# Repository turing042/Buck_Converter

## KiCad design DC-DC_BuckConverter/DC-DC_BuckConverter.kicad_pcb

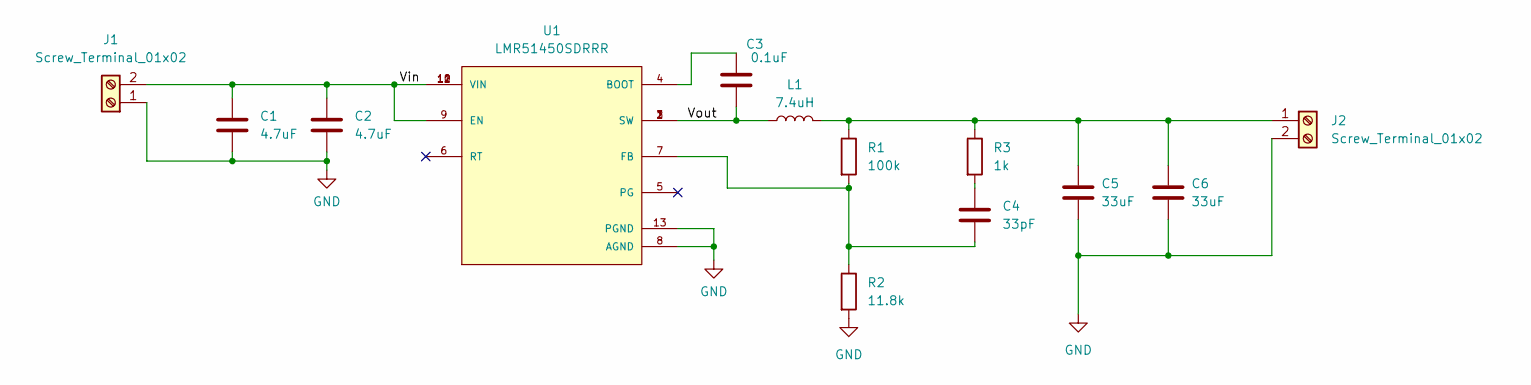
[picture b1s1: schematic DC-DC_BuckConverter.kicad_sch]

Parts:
C1, C2: 4.7uF; C_0603_1608Metric
C3: 0.1uF; C_0603_1608Metric
C4: 33pF; C_0603_1608Metric
C5, C6: 33uF; C_0603_1608Metric
J1, J2: Screw_Terminal_01x02; PhoenixContact_MSTBA_2,5_2-G-5,08_1x02_P5.08mm_Horizontal
L1: 7.4uH; L_Vishay_IHSM-4825
R1: 100k; R_0603_1608Metric
R2: 11.8k; R_0603_1608Metric
R3: 1k; R_0603_1608Metric
U1: LMR51450SDRRR; CONV_LMR51450SDRRR; PARTREV December 2022

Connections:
/Vin: C1.1, C2.1, J1.2, U1.9 (EN), U1.10 (VIN), U1.11 (VIN), U1.12 (VIN)
/Vout: C3.2, L1.1, U1.1 (SW), U1.2 (SW), U1.3 (SW)
GND: C1.2, C2.2, C5.2, C6.2, J1.1, J2.2, R2.2, U1.8 (AGND), U1.13 (PGND), U1.14, U1.15, U1.16
unnamed: C4.1, R3.2
unnamed: C5.1, C6.1, J2.1, L1.2, R1.1, R3.1
unnamed: C3.1, U1.4 (BOOT)
unnamed: C4.2, R1.2, R2.1, U1.7 (FB)

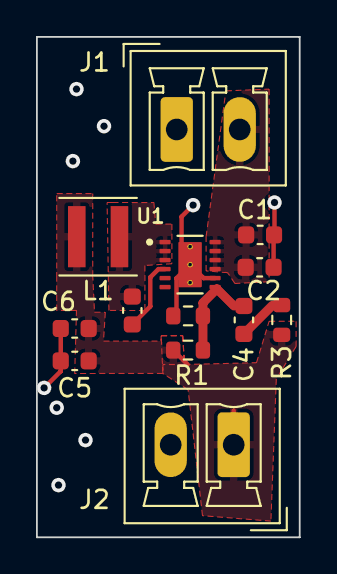
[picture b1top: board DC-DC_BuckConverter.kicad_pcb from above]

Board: 4 copper layers, 14.6 x 27.8 mm, 13 parts (0 on the bottom side), 7 nets.

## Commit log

2025-09-16 Create Arduino_code
